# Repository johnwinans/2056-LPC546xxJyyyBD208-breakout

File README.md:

# 2056-LPC546xxJyyyBD208-breakout

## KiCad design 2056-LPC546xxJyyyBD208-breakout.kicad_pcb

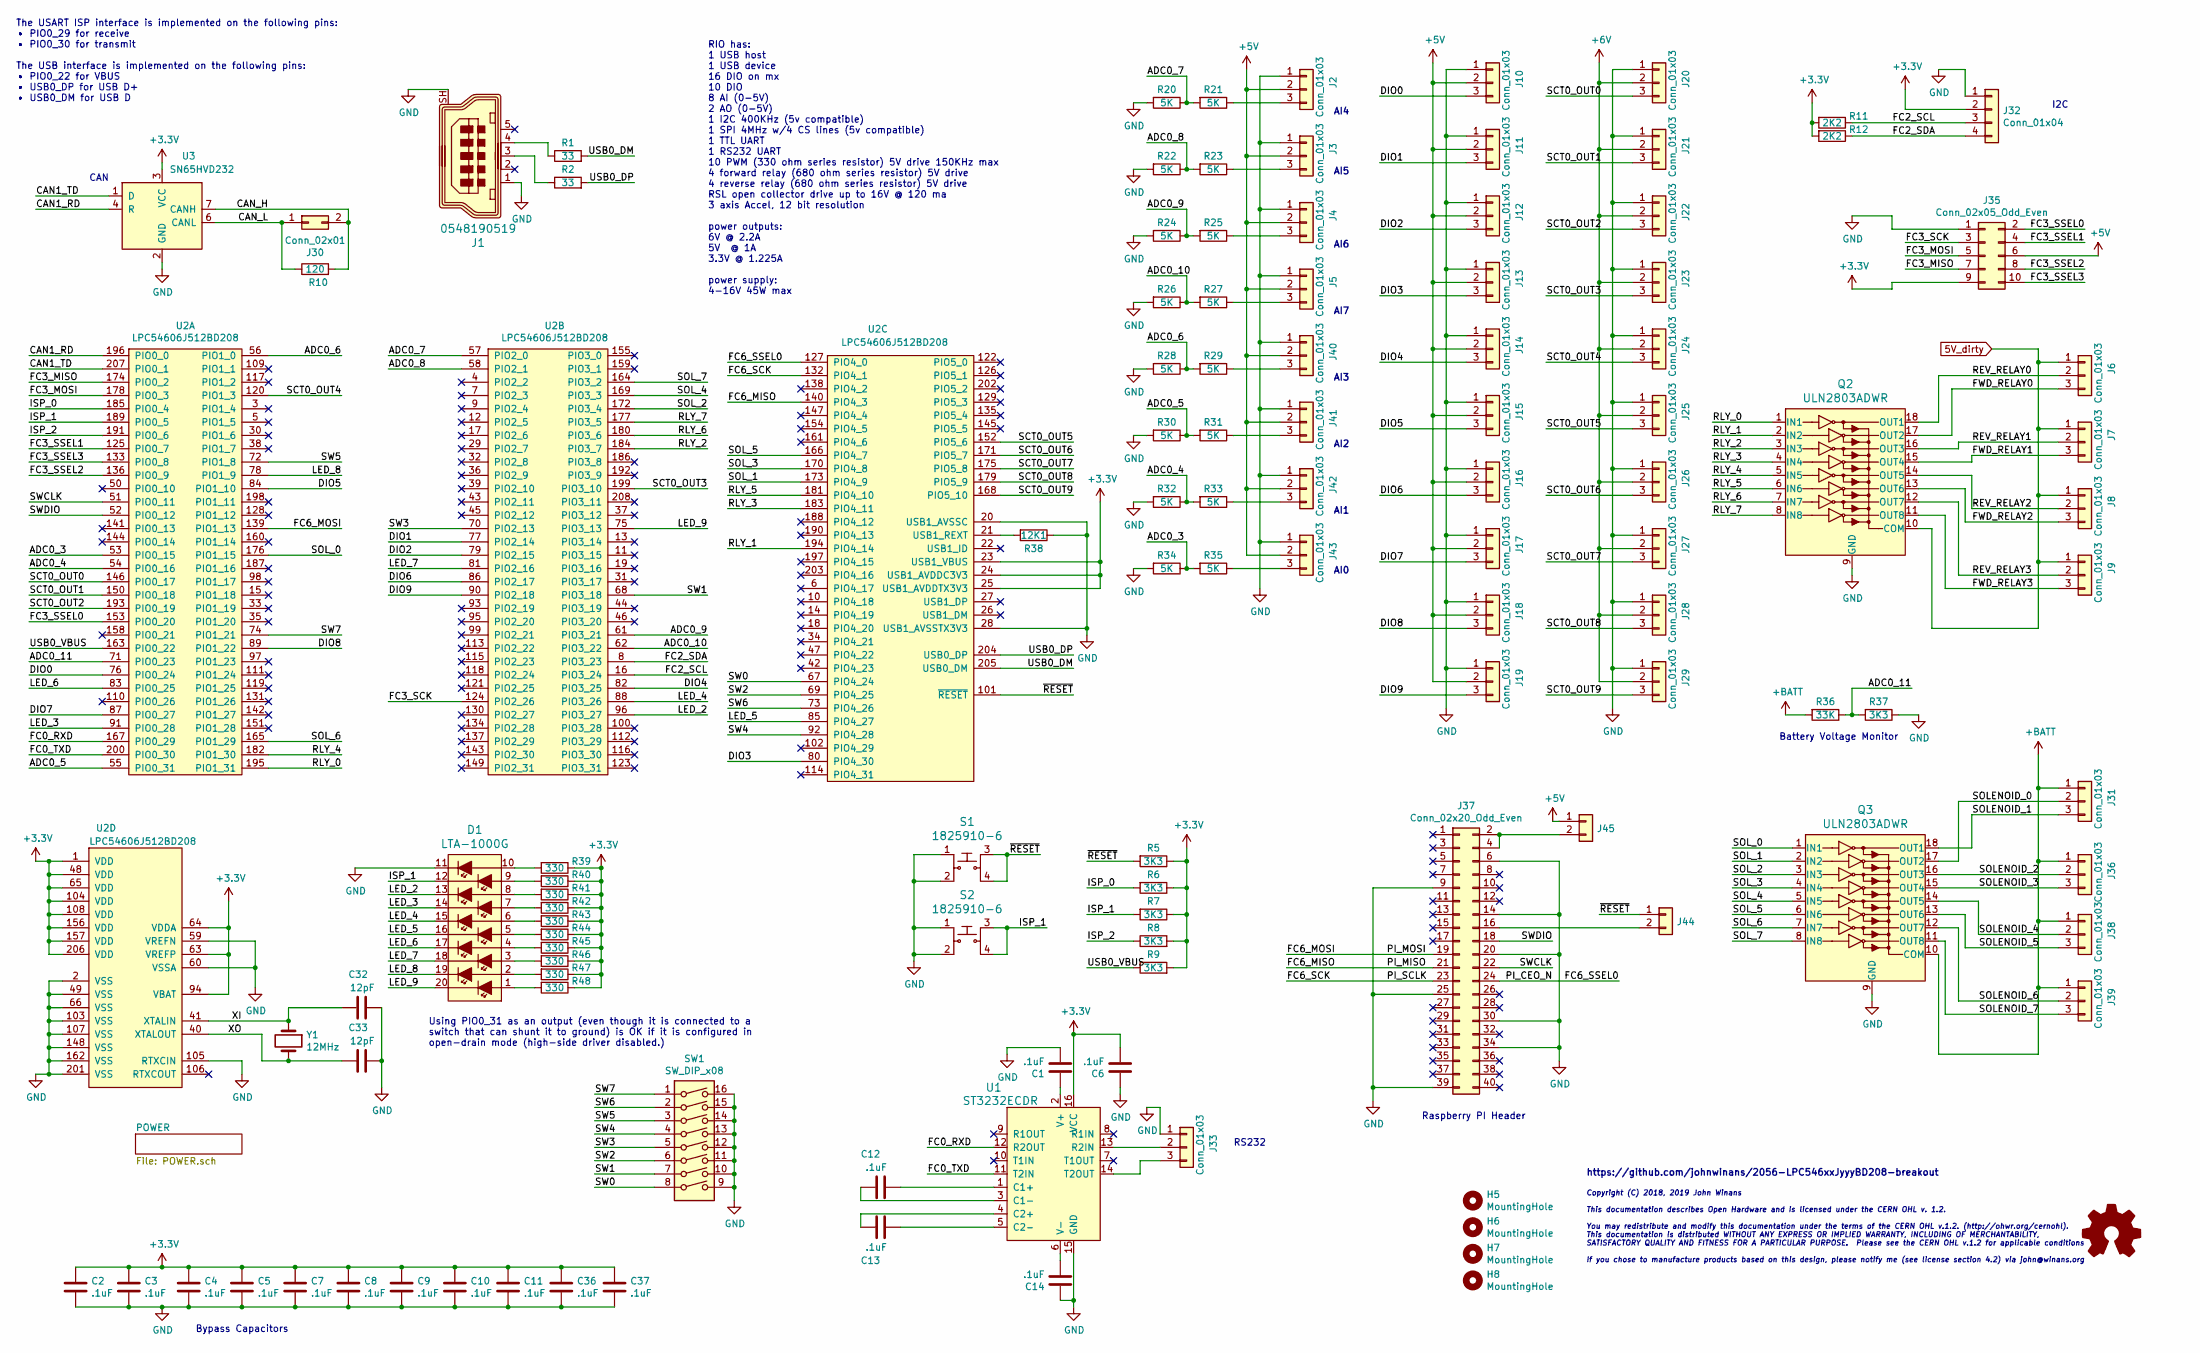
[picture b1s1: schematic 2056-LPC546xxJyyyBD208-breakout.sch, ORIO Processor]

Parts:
C1, C2, C3, C4, C5, C6, C7, C8, C9, C10, C11, C12, C13, C14, C36, C37: .1uF; C_0603_1608Metric_Pad1.05x0.95mm_HandSolder; Digi-Key_PN 445-6854-1-ND
C32, C33: 12pF; C_0603_1608Metric_Pad1.05x0.95mm_HandSolder; Digi-Key_PN 445-6854-1-ND
D1: LTA-1000G; LED_Bar_Graph_LTA-1000; MPN LTA-1000G; Digi-Key_PN 160-1067-ND
H5, H6, H7, H8: MountingHole; MountingHole_2.7mm_M2.5
J1: 0548190519; USB_Mini_B_Female_548190519; MPN 0548190519; Digi-Key_PN WM17115-ND
J2, J3, J4, J5, J6, J7, J8, J9, J10, J11, J12, J13, J14, J15, J16, J17, J18, J19, J20, J21, J22, J23, J24, J25, J26, J27, J28, J29, J31, J33, J36, J38, J39, J40, J41, J42, J43: Conn_01x03; PinHeader_1x03_P2.54mm_Vertical; Digi-Key_PN 2057-PH1-03-UA-ND
J30: Conn_02x01; PinHeader_1x02_P2.54mm_Vertical; Digi-Key_PN 2057-PH1-02-UA-ND
J32: Conn_01x04; PinHeader_1x04_P2.54mm_Vertical; Digi-Key_PN 2057-PH1-04-UA-ND
J35: Conn_02x05_Odd_Even; PinHeader_2x05_P2.54mm_Vertical
J37: Conn_02x20_Odd_Even; PinHeader_2x20_P2.54mm_Vertical; Digi-Key_PN PH2-20-UA
J44, J45: Conn_01x02; PinHeader_1x02_P2.54mm_Vertical
LOGO1: Logo_Open_Hardware_Small; OSHW-Logo_11.4x12mm_SilkScreen
Q2, Q3: ULN2803ADWR; SOIC-18_W7.5mm; MPN ULN2803ADWR; Digi-Key_PN 296-15777-1-ND
R1, R2: 33; R_0603_1608Metric_Pad1.05x0.95mm_HandSolder; Digi-Key_PN 311-33.0HRCT-ND
R5, R6, R7, R8, R9, R37: 3K3; R_0603_1608Metric_Pad1.05x0.95mm_HandSolder; Digi-Key_PN 311-3.30KHRCT-ND
R10: 120; R_0603_1608Metric_Pad1.05x0.95mm_HandSolder; Digi-Key_PN 311-120HRCT-ND
R11, R12: 2K2; R_0603_1608Metric_Pad1.05x0.95mm_HandSolder; Digi-Key_PN 311-2.20KHRCT-ND
R20, R21, R22, R23, R24, R25, R26, R27, R28, R29, R30, R31, R32, R33, R34, R35: 5K; R_0603_1608Metric_Pad1.05x0.95mm_HandSolder
R36: 33K; R_0603_1608Metric_Pad1.05x0.95mm_HandSolder; Digi-Key_PN 311-33.0KHRCT-ND
R38: 12K1; R_0603_1608Metric_Pad1.05x0.95mm_HandSolder; Digi-Key_PN 311-12.1KHRCT-ND
R39, R40, R41, R42, R43, R44, R45, R46, R47, R48: 330; R_0603_1608Metric_Pad1.05x0.95mm_HandSolder
S1, S2: 1825910-6; Switch_Tactile_THT_6x6mm; MPN 1825910-6; Digi-Key_PN 450-1650-ND
SW1: SW_DIP_x08; SW_DIP_SPSTx08_Slide_6.7x21.88mm_W7.62mm_P2.54mm_LowProfile; Digi-Key_PN CT2108MS-ND
U1: ST3232ECDR; SOIC-16_3.9x9.9mm_P1.27mm; MPN ST3232ECDR; Digi-Key_PN 497-6537-1-ND
U2: LPC54606J512BD208; LQFP-208_28x28mm_P0.5mm; Digi-Key_PN 568-13367-ND
U3: SN65HVD232; SOIC-8_3.9x4.9mm_P1.27mm; Digi-Key_PN 296-26344-1-ND
Y1: 12MHz; Crystal_SMD_5032-2Pin_5.0x3.2mm_HandSoldering; Digi-Key_PN 644-1034-1-ND

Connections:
5V_dirty: J6.1, J7.1, J8.1, J9.1, Q2.10 (COM); also elsewhere on the board
+3V3: C2.1, C3.1, C4.1, C5.1, C6.2, C7.1, C8.1, C9.1, C10.1, C11.1, C36.1, C37.1, J32.2, J35.9, R5.1, R6.1, R7.1, R8.2, R9.2, R11.2, R12.2, R39.1, R40.1, R41.1, R42.1, R43.1, R44.1, R45.1, R46.1, R47.1, R48.1, U1.16 (VCC), U2.1 (VDD), U2.23 (USB1_VBUS), U2.24 (USB1_AVDDC3V3), U2.25 (USB1_AVDDTX3V3), U2.48 (VDD), U2.63 (VREFP), U2.64 (VDDA), U2.65 (VDD), U2.94 (VBAT), U2.104 (VDD), U2.108 (VDD), U2.156 (VDD), U2.157 (VDD), U2.206 (VDD), U3.3 (VCC); also elsewhere on the board
+5V: J2.2, J3.2, J4.2, J5.2, J10.2, J11.2, J12.2, J13.2, J14.2, J15.2, J16.2, J17.2, J18.2, J19.2, J35.6, J40.2, J41.2, J42.2, J43.2, J45.1; also elsewhere on the board
+6V: J20.2, J21.2, J22.2, J23.2, J24.2, J25.2, J26.2, J27.2, J28.2, J29.2; also elsewhere on the board
+BATT: J31.1, J36.1, J38.1, J39.1, Q3.10 (COM), R36.2; also elsewhere on the board
/ADC0_3: R34.1, R35.2, U2.53 (PIO0_15)
/ADC0_4: R32.1, R33.2, U2.54 (PIO0_16)
/ADC0_5: R30.1, R31.2, U2.55 (PIO0_31)
/ADC0_6: R28.1, R29.2, U2.56 (PIO1_0)
/ADC0_7: R20.1, R21.2, U2.57 (PIO2_0)
/ADC0_8: R22.1, R23.2, U2.58 (PIO2_1)
/ADC0_9: R24.1, R25.2, U2.61 (PIO3_21)
/ADC0_10: R26.1, R27.2, U2.62 (PIO3_22)
/ADC0_11: R36.1, R37.2, U2.71 (PIO0_23)
/CAN1_RD: U2.196 (PIO0_0), U3.4 (R)
/CAN1_TD: U2.207 (PIO0_1), U3.1 (D)
/CAN_H: J30.2, R10.2, U3.7 (CANH)
/CAN_L: J30.1, R10.1, U3.6 (CANL)
/DIO0: J10.3, U2.76 (PIO0_24)
/DIO1: J11.3, U2.77 (PIO2_14)
/DIO2: J12.3, U2.79 (PIO2_15)
/DIO3: J13.3, U2.80 (PIO4_30)
/DIO4: J14.3, U2.82 (PIO3_25)
/DIO5: J15.3, U2.84 (PIO1_10)
/DIO6: J16.3, U2.86 (PIO2_17)
/DIO7: J17.3, U2.87 (PIO0_27)
/DIO8: J18.3, U2.89 (PIO1_22)
/DIO9: J19.3, U2.90 (PIO2_18)
/FC0_RXD: U1.12 (R2OUT), U2.167 (PIO0_29)
/FC0_TXD: U1.11 (T2IN), U2.200 (PIO0_30)
/FC2_SCL: J32.3, R11.1, U2.16 (PIO3_24)
/FC2_SDA: J32.4, R12.1, U2.8 (PIO3_23)
/FC3_MISO: J35.7, U2.174 (PIO0_2)
/FC3_MOSI: J35.5, U2.178 (PIO0_3)
/FC3_SCK: J35.3, U2.124 (PIO2_26)
/FC3_SSEL0: J35.2, U2.153 (PIO0_20)
/FC3_SSEL1: J35.4, U2.125 (PIO0_7)
/FC3_SSEL2: J35.8, U2.136 (PIO0_9)
/FC3_SSEL3: J35.10, U2.133 (PIO0_8)
/FC6_MISO: J37.21, U2.140 (PIO4_3)
/FC6_MOSI: J37.19, U2.139 (PIO1_13)
/FC6_SCK: J37.23, U2.132 (PIO4_1)
/FC6_SSEL0: J37.24, U2.127 (PIO4_0)
/FWD_RELAY0: J6.3, Q2.17 (OUT2)
/FWD_RELAY1: J7.3, Q2.15 (OUT4)
/FWD_RELAY2: J8.3, Q2.13 (OUT6)
/FWD_RELAY3: J9.3, Q2.11 (OUT8)
/ISP_0: R6.2, U2.185 (PIO0_4)
/ISP_1: D1.12, R7.2, S2.3, S2.4, U2.189 (PIO0_5)
/ISP_2: R8.1, U2.191 (PIO0_6)
/LED_2: D1.13, U2.96 (PIO3_27)
/LED_3: D1.14, U2.91 (PIO0_28)
/LED_4: D1.15, U2.88 (PIO3_26)
/LED_5: D1.16, U2.85 (PIO4_27)
/LED_6: D1.17, U2.83 (PIO0_25)
/LED_7: D1.18, U2.81 (PIO2_16)
/LED_8: D1.19, U2.78 (PIO1_9)
/LED_9: D1.20, U2.75 (PIO3_13)
/REV_RELAY0: J6.2, Q2.18 (OUT1)
/REV_RELAY1: J7.2, Q2.16 (OUT3)
/REV_RELAY2: J8.2, Q2.14 (OUT5)
/REV_RELAY3: J9.2, Q2.12 (OUT7)
/RLY_0: Q2.1 (IN1), U2.195 (PIO1_31)
/RLY_1: Q2.2 (IN2), U2.194 (PIO4_14)
/RLY_2: Q2.3 (IN3), U2.184 (PIO3_7)
/RLY_3: Q2.4 (IN4), U2.183 (PIO4_11)
/RLY_4: Q2.5 (IN5), U2.182 (PIO1_30)
/RLY_5: Q2.6 (IN6), U2.181 (PIO4_10)
/RLY_6: Q2.7 (IN7), U2.180 (PIO3_6)
/RLY_7: Q2.8 (IN8), U2.177 (PIO3_5)
/SCT0_OUT0: J20.3, U2.146 (PIO0_17)
/SCT0_OUT1: J21.3, U2.150 (PIO0_18)
/SCT0_OUT2: J22.3, U2.193 (PIO0_19)
/SCT0_OUT3: J23.3, U2.199 (PIO3_10)
/SCT0_OUT4: J24.3, U2.120 (PIO1_3)
/SCT0_OUT5: J25.3, U2.152 (PIO5_6)
/SCT0_OUT6: J26.3, U2.171 (PIO5_7)
/SCT0_OUT7: J27.3, U2.175 (PIO5_8)
/SCT0_OUT8: J28.3, U2.179 (PIO5_9)
/SCT0_OUT9: J29.3, U2.168 (PIO5_10)
/SOLENOID_0: J31.2, Q3.17 (OUT2)
/SOLENOID_1: J31.3, Q3.18 (OUT1)
/SOLENOID_2: J36.2, Q3.16 (OUT3)
/SOLENOID_3: J36.3, Q3.15 (OUT4)
/SOLENOID_4: J38.2, Q3.14 (OUT5)
/SOLENOID_5: J38.3, Q3.13 (OUT6)
/SOLENOID_6: J39.2, Q3.12 (OUT7)
/SOLENOID_7: J39.3, Q3.11 (OUT8)
/SOL_0: Q3.1 (IN1), U2.176 (PIO1_15)
/SOL_1: Q3.2 (IN2), U2.173 (PIO4_9)
/SOL_2: Q3.3 (IN3), U2.172 (PIO3_4)
/SOL_3: Q3.4 (IN4), U2.170 (PIO4_8)
/SOL_4: Q3.5 (IN5), U2.169 (PIO3_3)
/SOL_5: Q3.6 (IN6), U2.166 (PIO4_7)
/SOL_6: Q3.7 (IN7), U2.165 (PIO1_29)
/SOL_7: Q3.8 (IN8), U2.164 (PIO3_2)
/SW0: SW1.8, U2.67 (PIO4_24)
/SW1: SW1.7, U2.68 (PIO3_18)
/SW2: SW1.6, U2.69 (PIO4_25)
/SW3: SW1.5, U2.70 (PIO2_13)
/SW4: SW1.4, U2.92 (PIO4_28)
/SW5: SW1.3, U2.72 (PIO1_8)
/SW6: SW1.2, U2.73 (PIO4_26)
/SW7: SW1.1, U2.74 (PIO1_21)
/SWCLK: J37.22, U2.51 (PIO0_11)
/SWDIO: J37.18, U2.52 (PIO0_12)
/USB0_DM: R1.2, U2.205 (USB0_DM)
/USB0_DP: R2.2, U2.204 (USB0_DP)
/USB0_VBUS: R9.1, U2.163 (PIO0_22)
/XI: C32.1, U2.41 (XTALIN), Y1.1
/XO: C33.1, U2.40 (XTALOUT), Y1.2
/~RESET~: J44.1, R5.2, S1.3, S1.4, U2.101 (~RESET)
GND: C1.2, C2.2, C3.2, C4.2, C5.2, C6.1, C7.2, C8.2, C9.2, C10.2, C11.2, C14.1, C32.2, C33.2, C36.2, C37.2, D1.11, J1.1, J1.SH, J2.1, J3.1, J4.1, J5.1, J10.1, J11.1, J12.1, J13.1, J14.1, J15.1, J16.1, J17.1, J18.1, J19.1, J20.1, J21.1, J22.1, J23.1, J24.1, J25.1, J26.1, J27.1, J28.1, J29.1, J32.1, J33.1, J35.1, J37.6, J37.9, J37.14, J37.20, J37.25, J37.30, J37.34, J37.39, J40.1, J41.1, J42.1, J43.1, Q2.9 (GND), Q3.9 (GND), R20.2, R22.2, R24.2, R26.2, R28.2, R30.2, R32.2, R34.2, R37.1, R38.1, S1.1, S1.2, S2.1, S2.2, SW1.9, SW1.10, SW1.11, SW1.12, SW1.13, SW1.14, SW1.15, SW1.16, U1.15 (GND), U2.2 (VSS), U2.20 (USB1_AVSSC), U2.28 (USB1_AVSSTX3V3), U2.49 (VSS), U2.59 (VREFN), U2.60 (VSSA), U2.66 (VSS), U2.103 (VSS), U2.105 (RTXCIN), U2.107 (VSS), U2.148 (VSS), U2.162 (VSS), U2.201 (VSS), U3.2 (GND); also elsewhere on the board
unnamed: C1.1, U1.2 (V+)
unnamed: C12.1, U1.3 (C1-)
unnamed: C12.2, U1.1 (C1+)
unnamed: C13.1, U1.4 (C2+)
unnamed: C13.2, U1.5 (C2-)
unnamed: C14.2, U1.6 (V-)
unnamed: D1.1, R48.2
unnamed: D1.2, R47.2
unnamed: D1.3, R46.2
unnamed: D1.4, R45.2
unnamed: D1.5, R44.2
unnamed: D1.6, R43.2
unnamed: D1.7, R42.2
unnamed: D1.8, R41.2
unnamed: D1.9, R40.2
unnamed: D1.10, R39.2
unnamed: J1.3, R2.1
unnamed: J1.4, R1.1
unnamed: J2.3, R21.1
unnamed: J3.3, R23.1
unnamed: J4.3, R25.1
unnamed: J5.3, R27.1
unnamed: J33.2, U1.13 (R2IN)
unnamed: J33.3, U1.14 (T2OUT)
unnamed: J37.2, J37.4, J45.2
unnamed: J37.16, J44.2
unnamed: J40.3, R29.1
unnamed: J41.3, R31.1
unnamed: J42.3, R33.1
unnamed: J43.3, R35.1
unnamed: R38.2, U2.21 (USB1_REXT)

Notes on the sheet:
Bypass Capacitors
Copyright (C) 2018, 2019 John Winans This documentation describes Open Hardware and is licensed under the CERN OHL v. 1.2. You may redistribute and modify this documentation under the terms of the CERN OHL v.1.2. (http://ohwr.org/cernohl). This documentation is distributed WITHOUT ANY EXPRESS OR IM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
The USART ISP interface is implemented on the following pins: • PIO0_29 for receive • PIO0_30 for transmit The USB interface is implemented on the following pins: • PIO0_22 for VBUS • USB0_DP for USB D+ • USB0_DM for USB D
https://github.com/johnwinans/2056-LPC546xxJyyyBD208-breakout
RIO has: 1 USB host 1 USB device 16 DIO on mx 10 DIO 8 AI (0-5V) 2 AO (0-5V) 1 I2C 400KHz (5v compatible) 1 SPI 4MHz w/4 CS lines (5v compatible) 1 TTL UART 1 RS232 UART 10 PWM (330 ohm series resistor) 5V drive 150KHz max 4 forward relay (680 ohm series resistor) 5V drive 4 reverse relay (680 ohm 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
I2C
CAN
Using PIO0_31 as an output (even though it is connected to a switch that can shunt it to ground) is OK if it is configured in open-drain mode (high-side driver disabled.)
Raspberry PI Header
RS232
Battery Voltage Monitor
AI0
AI1
AI2
AI3
AI7
AI6
AI5
AI4

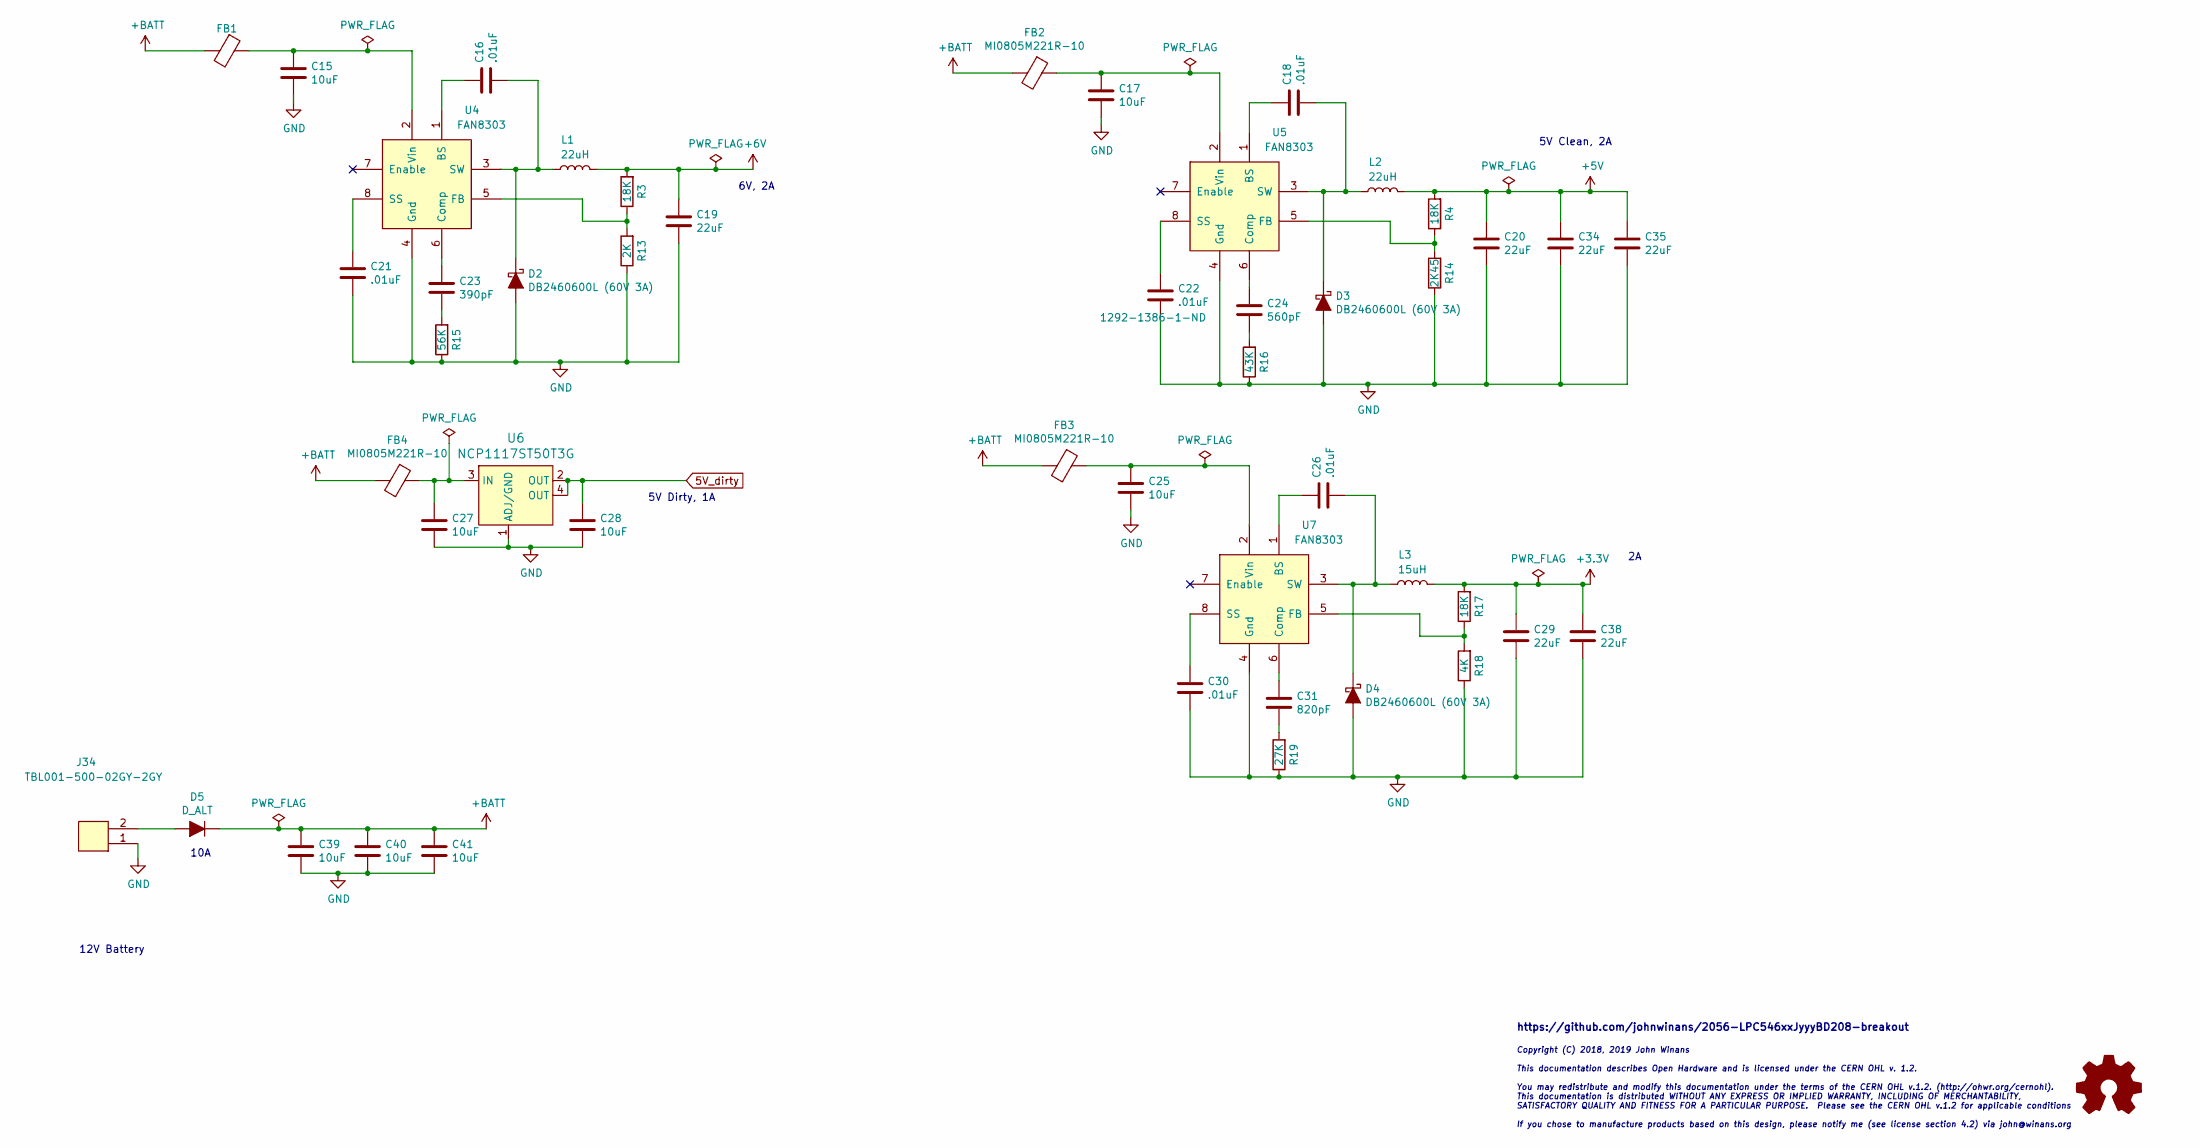
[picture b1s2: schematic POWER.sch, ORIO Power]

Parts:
C15, C17, C25, C27, C28, C39, C40, C41: 10uF; C_1206_3216Metric_Pad1.42x1.75mm_HandSolder; Digi-Key_PN 1276-1075-1-ND
C16, C18, C21, C22, C26, C30: .01uF; C_0603_1608Metric_Pad1.05x0.95mm_HandSolder; Digi-Key_PN 1292-1386-1-ND
C19, C20, C34, C35: 22uF; C_1210_3225Metric_Pad1.42x2.65mm_HandSolder; Digi-Key_PN 1276-6780-1-ND
C23: 390pF; C_0603_1608Metric_Pad1.05x0.95mm_HandSolder; Digi-Key_PN 1276-2049-1-ND
C24: 560pF; C_0603_1608Metric_Pad1.05x0.95mm_HandSolder; Digi-Key_PN 1276-1278-1-ND
C29, C38: 22uF; C_0805_2012Metric_Pad1.15x1.40mm_HandSolder; Digi-Key_PN 1276-6780-1-ND
C31: 820pF; C_0603_1608Metric_Pad1.05x0.95mm_HandSolder; Digi-Key_PN 1276-2117-1-ND
D2, D3, D4: DB2460600L (60V 3A); D_1806_4516Metric_Pad1.57x1.80mm_HandSolder; Digi-Key_PN DB2460600LCT-ND
D5: D_ALT; D_SMC; Digi-Key_PN S10KCV7GCT-ND
FB1, FB2, FB3, FB4: MI0805M221R-10; L_0603_1608Metric_Pad1.05x0.95mm_HandSolder; Digi-Key_PN 240-2392-1-ND
J34: TBL001-500-02GY-2GY; Digi-Key_PN 102-6360-ND
L1, L2: 22uH; L_Taiyo-Yuden_NR-80xx_HandSoldering; MPN NR8040T220M; Digi-Key_PN 587-2002-1-ND
L3: 15uH; L_Taiyo-Yuden_NR-60xx_HandSoldering; Digi-Key_PN 587-2633-1-ND
R3, R4, R17: 18K; R_0603_1608Metric_Pad1.05x0.95mm_HandSolder; Digi-Key_PN 311-18.0KHRCT-ND
R13: 2K; R_0603_1608Metric_Pad1.05x0.95mm_HandSolder
R14: 2K45; R_0603_1608Metric_Pad1.05x0.95mm_HandSolder; Digi-Key_PN 311-2.43KHRCT-ND
R15: 56K; R_0603_1608Metric_Pad1.05x0.95mm_HandSolder; Digi-Key_PN CR0603-JW-563ELFCT-ND
R16: 43K; R_0603_1608Metric_Pad1.05x0.95mm_HandSolder; Digi-Key_PN 311-43.0KHRCT-ND
R18: 4K; R_0603_1608Metric_Pad1.05x0.95mm_HandSolder; Digi-Key_PN 311-4.02KHRCT-ND
R19: 27K; R_0603_1608Metric_Pad1.05x0.95mm_HandSolder; Digi-Key_PN 311-27.0KHRCT-ND
U4, U5, U7: FAN8303; SOIC-8_3.9x4.9mm_P1.27mm; Digi-Key_PN FAN8303MXCT-ND
U6: NCP1117ST50T3G; SOT-223; MPN NCP1117ST50T3G; Digi-Key_PN NCP1117ST50T3GOSCT-ND

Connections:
5V_dirty: C28.1, U6.2 (OUT), U6.4 (OUT); also elsewhere on the board
+3V3: C29.1, C38.1, L3.2, R17.2; also elsewhere on the board
+5V: C20.1, C34.1, C35.1, L2.2, R4.2; also elsewhere on the board
+6V: C19.1, L1.2, R3.2; also elsewhere on the board
+BATT: C39.1, C40.1, C41.1, D5.1 (K), FB1.2, FB2.2, FB3.2, FB4.2; also elsewhere on the board
GND: C15.2, C17.2, C19.2, C20.2, C21.2, C22.2, C25.2, C27.2, C28.2, C29.2, C30.2, C34.2, C35.2, C38.2, C39.2, C40.2, C41.2, D2.2 (A), D3.2 (A), D4.2 (A), J34.1, R13.1, R14.1, R15.1, R16.1, R18.1, R19.1, U4.4 (Gnd), U5.4 (Gnd), U6.1 (ADJ/GND), U7.4 (Gnd); also elsewhere on the board
unnamed: C15.1, FB1.1, U4.2 (Vin)
unnamed: C16.1, U4.1 (BS)
unnamed: C16.2, D2.1 (K), L1.1, U4.3 (SW)
unnamed: C17.1, FB2.1, U5.2 (Vin)
unnamed: C18.1, U5.1 (BS)
unnamed: C18.2, D3.1 (K), L2.1, U5.3 (SW)
unnamed: C21.1, U4.8 (SS)
unnamed: C22.1, U5.8 (SS)
unnamed: C23.1, U4.6 (Comp)
unnamed: C23.2, R15.2
unnamed: C24.1, U5.6 (Comp)
unnamed: C24.2, R16.2
unnamed: C25.1, FB3.1, U7.2 (Vin)
unnamed: C26.1, U7.1 (BS)
unnamed: C26.2, D4.1 (K), L3.1, U7.3 (SW)
unnamed: C27.1, FB4.1, U6.3 (IN)
unnamed: C30.1, U7.8 (SS)
unnamed: C31.1, U7.6 (Comp)
unnamed: C31.2, R19.2
unnamed: D5.2 (A), J34.2
unnamed: R3.1, R13.2, U4.5 (FB)
unnamed: R4.1, R14.2, U5.5 (FB)
unnamed: R17.1, R18.2, U7.5 (FB)

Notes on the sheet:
5V Clean, 2A
6V, 2A
5V Dirty, 1A
Copyright (C) 2018, 2019 John Winans This documentation describes Open Hardware and is licensed under the CERN OHL v. 1.2. You may redistribute and modify this documentation under the terms of the CERN OHL v.1.2. (http://ohwr.org/cernohl). This documentation is distributed WITHOUT ANY EXPRESS OR IM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
https://github.com/johnwinans/2056-LPC546xxJyyyBD208-breakout
12V Battery
10A

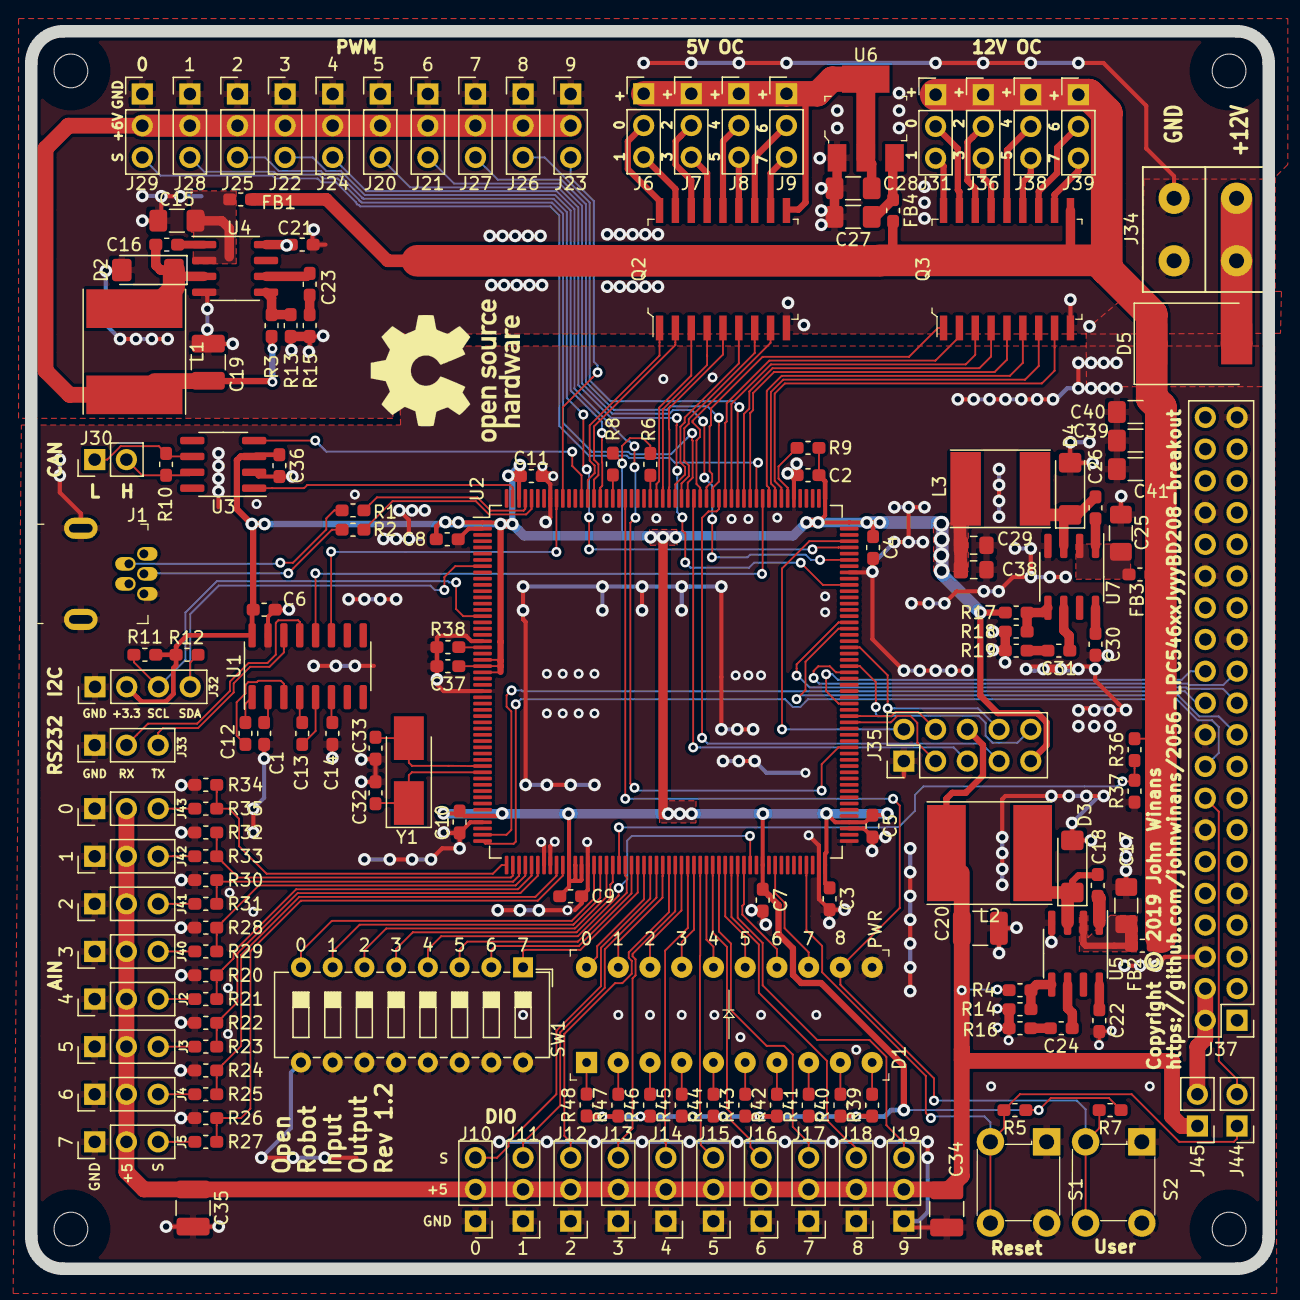
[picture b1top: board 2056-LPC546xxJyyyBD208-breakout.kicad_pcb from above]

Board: 2 copper layers, 99.1 x 99.1 mm, 164 parts (0 on the bottom side), 167 nets.

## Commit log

2019-10-06 First draft of the ORIO board.
2019-10-07 Cosmetic silkscreen & title block cleanup.
2019-10-11 Rev 1.1 first manufacturable draft.
2019-10-25 Correct CPU AVSSC pin.
2019-11-04 Fixed power on VSSC pin, add filter caps, power & reset jumpers, SWD.
2019-12-01 Added the cache.lib file for custom symbols.

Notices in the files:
2056-LPC546xxJyyyBD208-breakout.kicad_pcb:
Copyright © 2019 John Winans
2056-LPC546xxJyyyBD208-breakout.sch:
If you chose to manufacture products based on this design, please notify me (see license section 4.2) via john@winans.org
